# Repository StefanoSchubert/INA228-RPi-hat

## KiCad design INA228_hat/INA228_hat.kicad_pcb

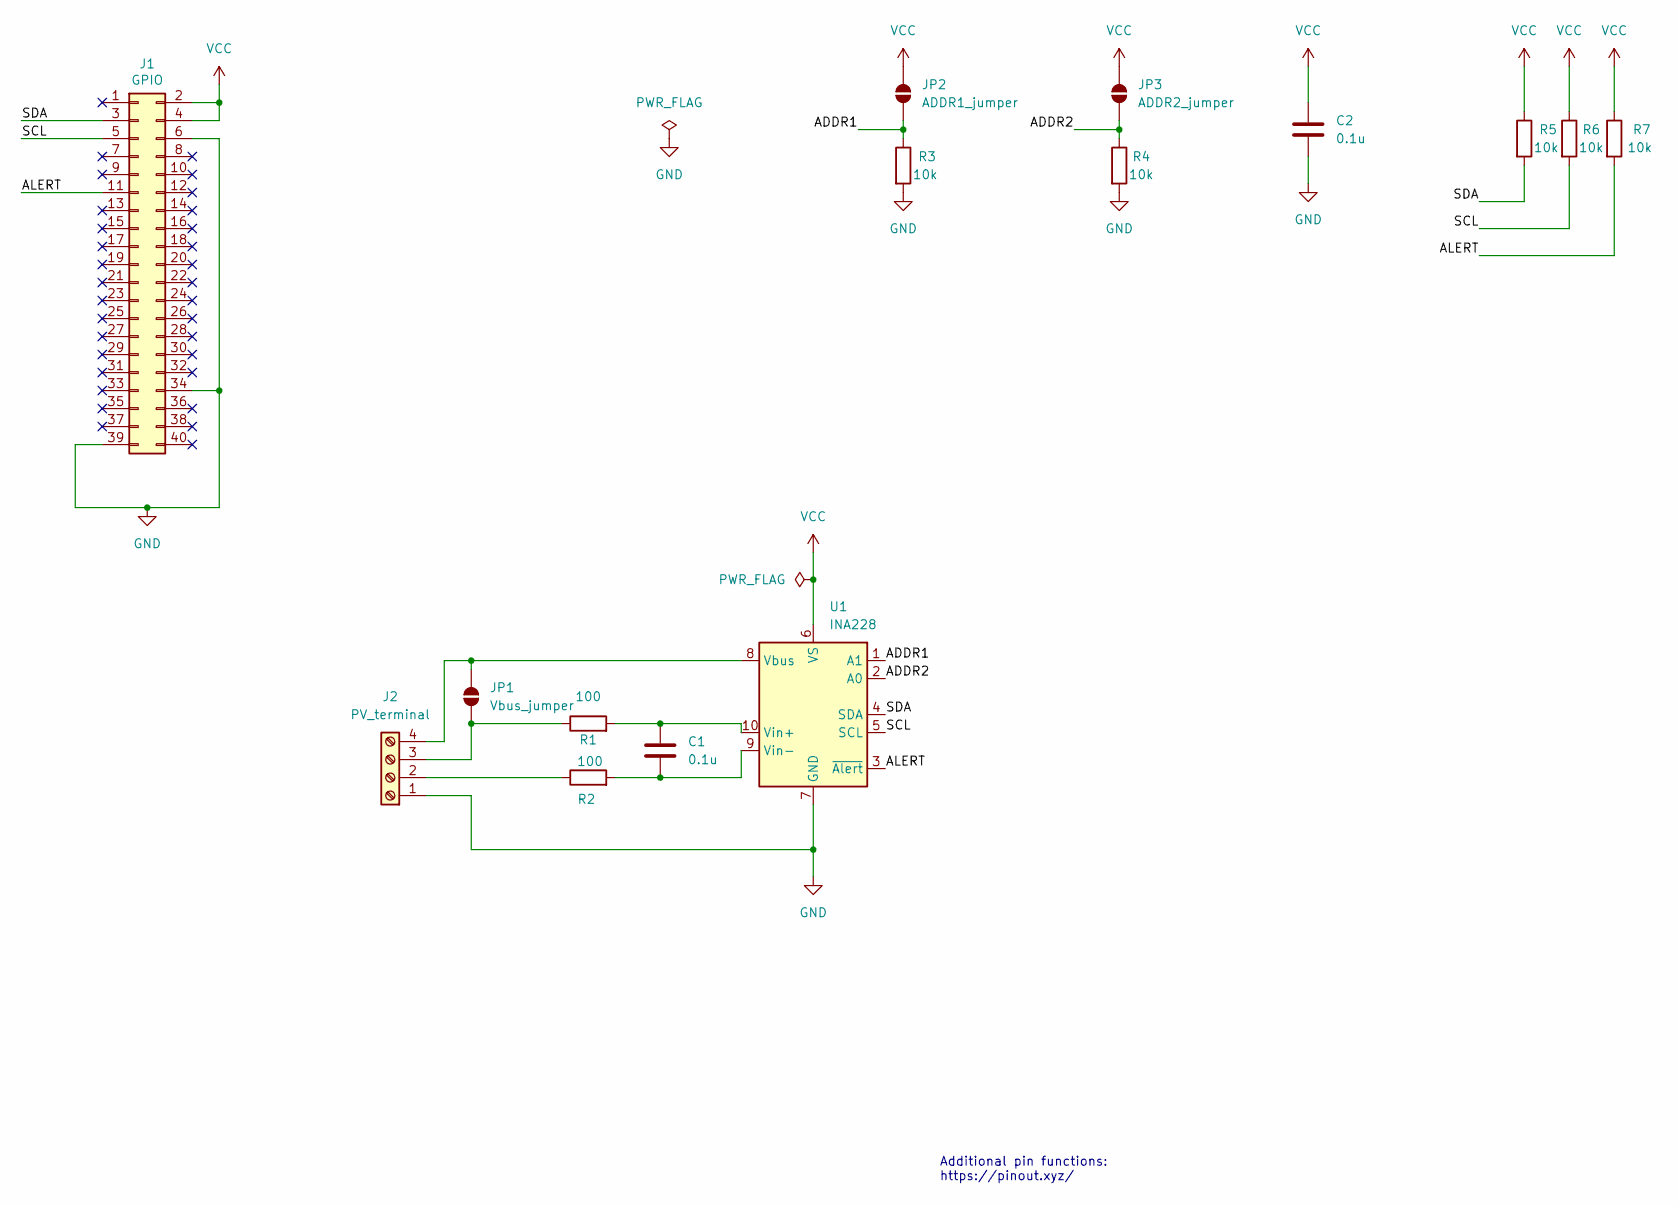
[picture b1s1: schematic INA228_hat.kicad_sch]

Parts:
C1, C2: 0.1u; C_1210_3225Metric
J1: GPIO; PinSocket_2x20_P2.54mm_Vertical
J2: PV_terminal; TerminalBlock_MetzConnect_Type094_RT03504HBLU_1x04_P5.00mm_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
JP1: Vbus_jumper; SolderJumper-2_P1.3mm_Open_TrianglePad1.0x1.5mm
JP2: ADDR1_jumper; SolderJumper-2_P1.3mm_Open_TrianglePad1.0x1.5mm
JP3: ADDR2_jumper; SolderJumper-2_P1.3mm_Open_TrianglePad1.0x1.5mm
R1, R2: 100; R_2512_6332Metric
R3, R4, R5, R6, R7: 10k; R_2512_6332Metric
U1: INA228; VSSOP10_DGS_TEX

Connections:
/ADDR1: JP2.1 (A), R3.1, U1.1 (A1)
/ADDR2: JP3.1 (A), R4.1, U1.2 (A0)
/ALERT: J1.11, R7.2, U1.3 (~Alert)
/SCL: J1.5, R6.2, U1.5 (SCL)
/SDA: J1.3, R5.2, U1.4 (SDA)
GND: C2.2, J1.6, J1.34, J1.39, J2.1, R3.2, R4.2, U1.7 (GND)
unnamed: J2.2, R2.1
unnamed: J2.3, JP1.1 (A), R1.1
unnamed: J2.4, JP1.2 (B), U1.8 (Vbus)
unnamed: C1.2, R1.2, U1.10 (Vin+)
unnamed: C1.1, R2.2, U1.9 (Vin-)
VCC: C2.1, J1.2, J1.4, JP2.2 (B), JP3.2 (B), R5.1, R6.1, R7.1, U1.6 (VS)

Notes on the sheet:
Additional pin functions: https://pinout.xyz/

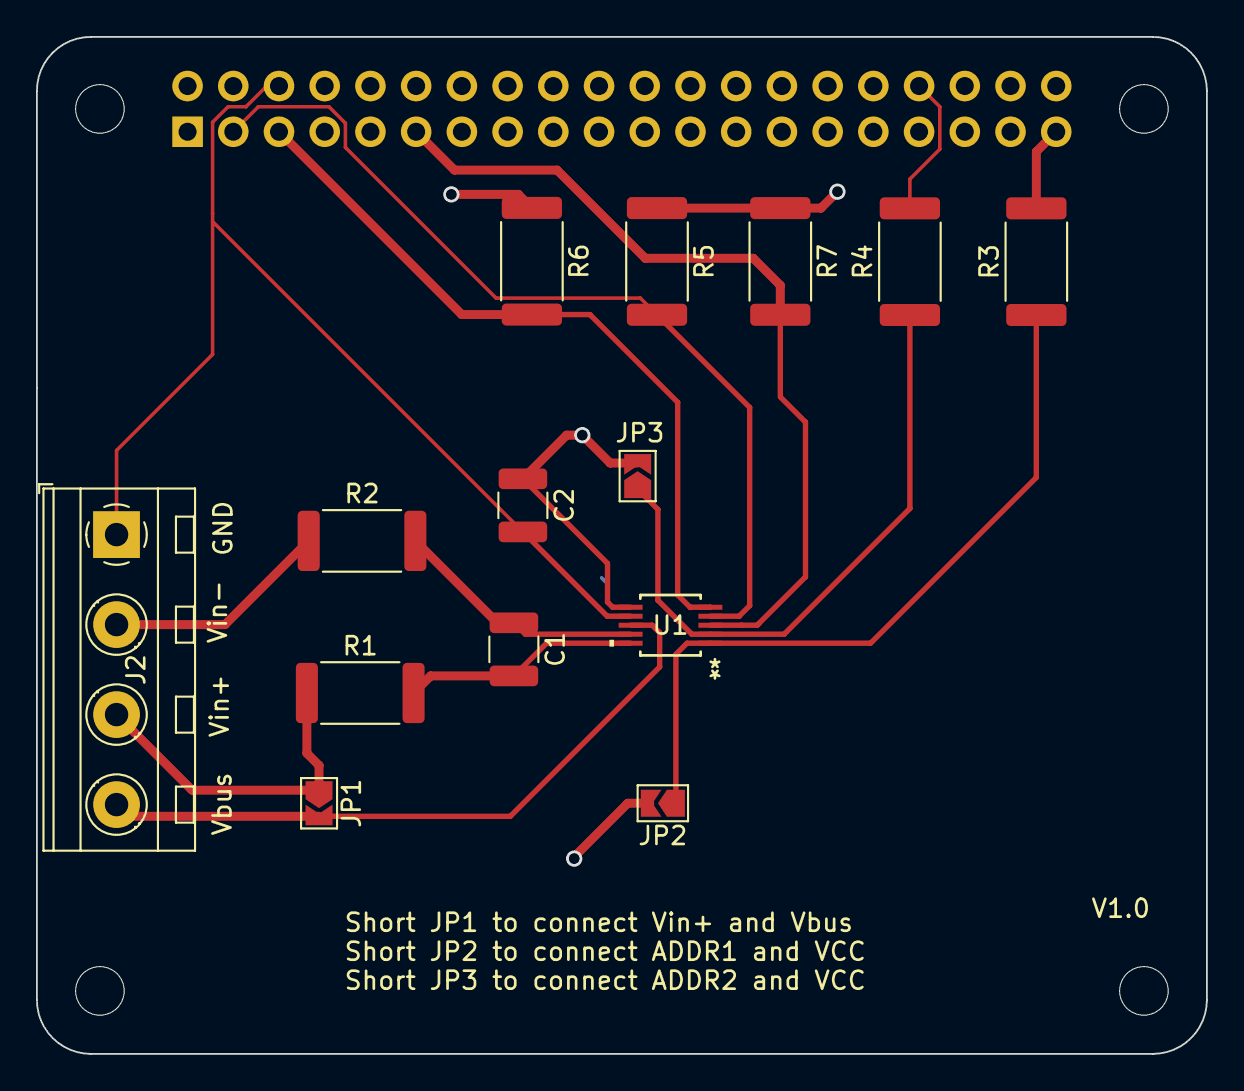
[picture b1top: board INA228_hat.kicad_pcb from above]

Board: 2 copper layers, 65.0 x 56.5 mm, 19 parts (1 on the bottom side), 12 nets.

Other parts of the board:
MH1, MH2, MH3, MH4: MountingHole_2.7mm_M2.5
